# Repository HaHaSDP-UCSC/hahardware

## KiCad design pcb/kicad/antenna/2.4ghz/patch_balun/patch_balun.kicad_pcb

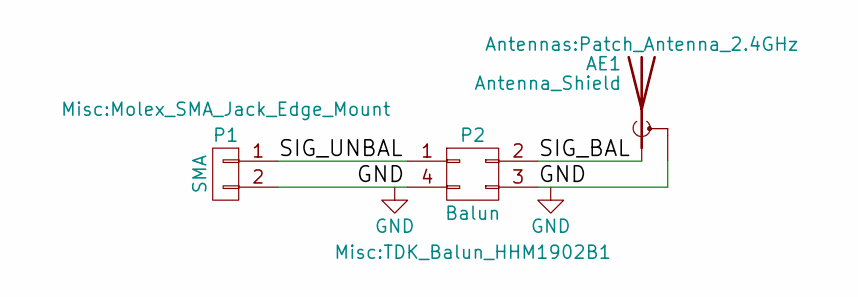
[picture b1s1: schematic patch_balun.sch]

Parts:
AE1: Antenna_Shield; Patch_Antenna_2.4GHz
P1: SMA; Molex_SMA_Jack_Edge_Mount
P2: Balun; TDK_Balun_HHM1902B1

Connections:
/SIG_BAL: AE1.1 (A), P2.2
/SIG_UNBAL: P1.1, P2.1
GND: AE1.2 (Shield), P1.2, P2.3, P2.4

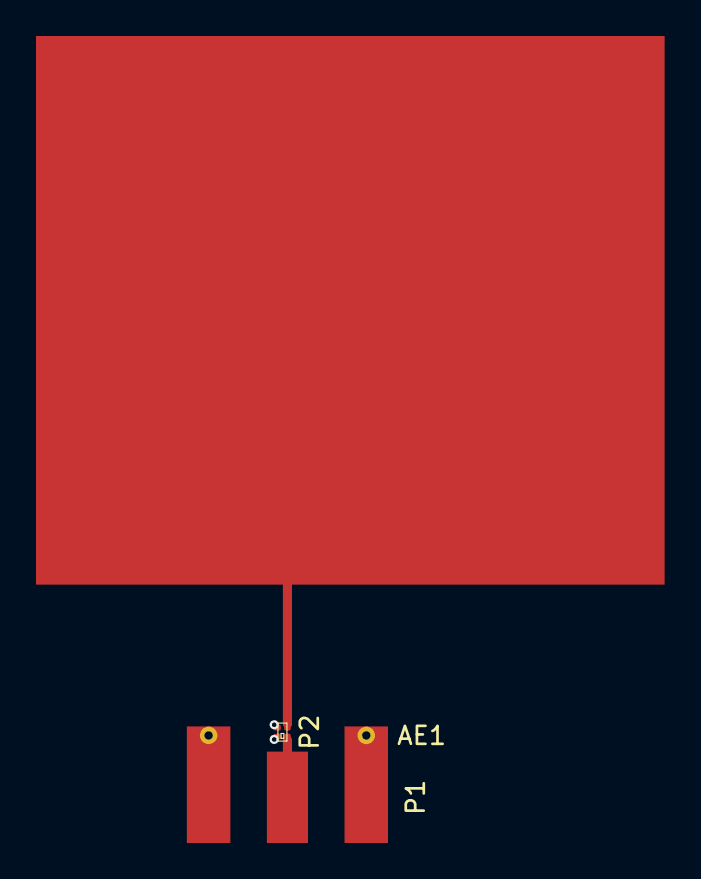
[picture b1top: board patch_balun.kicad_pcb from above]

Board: 2 copper layers, 3 parts (0 on the bottom side), 3 nets.
